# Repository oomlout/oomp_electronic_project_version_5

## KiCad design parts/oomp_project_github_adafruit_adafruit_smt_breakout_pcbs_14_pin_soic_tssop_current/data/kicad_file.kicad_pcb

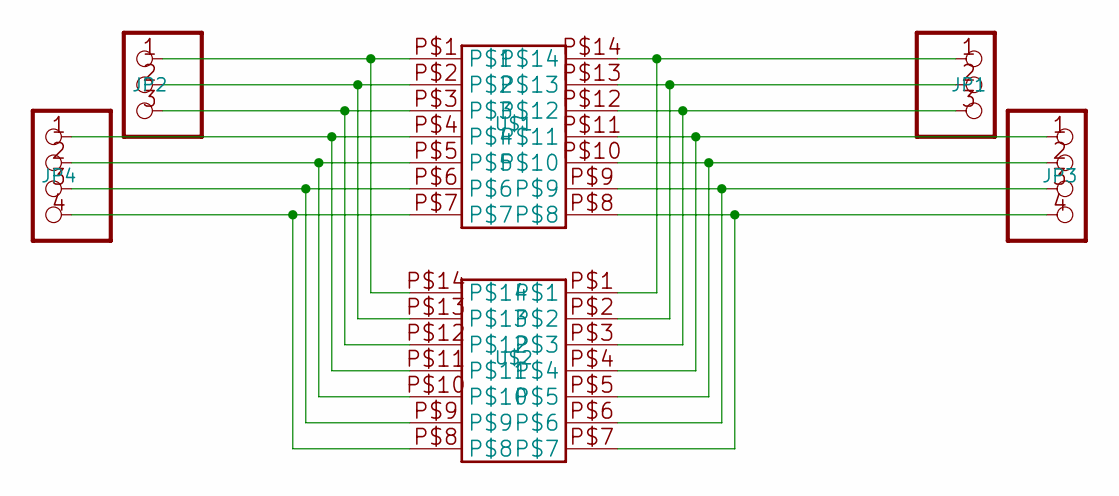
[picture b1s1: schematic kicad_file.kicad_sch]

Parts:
JP1, JP2: PADS-3
JP3, JP4: PADS-4
U$1: 14-PINSOIC-NW; SO14-NW
U$2: 14-PINTSSOP-NW; TSSOP14-NW

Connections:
unnamed: JP2.1, U$1.P$1, U$2.P$14
unnamed: JP2.2, U$1.P$2, U$2.P$13
unnamed: JP2.3, U$1.P$3, U$2.P$12
unnamed: JP4.1, U$1.P$4, U$2.P$11
unnamed: JP4.2, U$1.P$5, U$2.P$10
unnamed: JP4.3, U$1.P$6, U$2.P$9
unnamed: JP4.4, U$1.P$7, U$2.P$8
unnamed: JP1.1, U$1.P$14, U$2.P$1
unnamed: JP1.2, U$1.P$13, U$2.P$2
unnamed: JP1.3, U$1.P$12, U$2.P$3
unnamed: JP3.1, U$1.P$11, U$2.P$4
unnamed: JP3.2, U$1.P$10, U$2.P$5
unnamed: JP3.3, U$1.P$9, U$2.P$6
unnamed: JP3.4, U$1.P$8, U$2.P$7

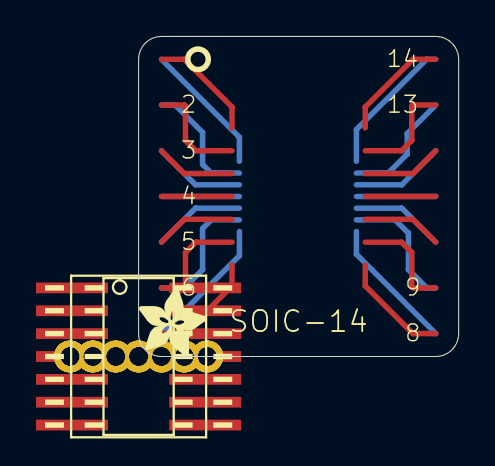
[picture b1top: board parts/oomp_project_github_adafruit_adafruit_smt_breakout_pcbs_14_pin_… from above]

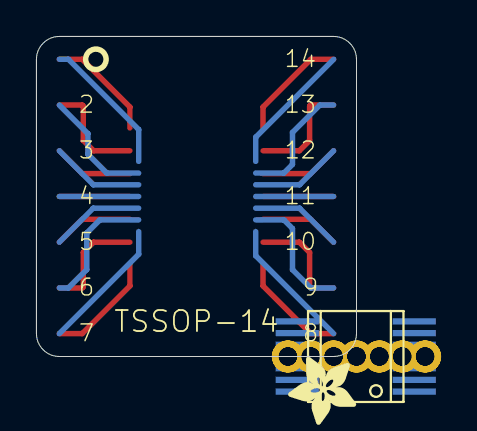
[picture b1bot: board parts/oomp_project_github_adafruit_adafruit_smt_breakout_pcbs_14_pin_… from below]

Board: 2 copper layers, 17.8 x 17.8 mm, 8 parts (2 on the bottom side), 14 nets.

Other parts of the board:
U$3, U$4: ADAFRUIT_3.5MM

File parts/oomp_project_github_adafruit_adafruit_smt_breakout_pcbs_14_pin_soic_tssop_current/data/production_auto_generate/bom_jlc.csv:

Comment,Designator,Footprint,LCSC Part #
,"U$3,U$4",14-pin SOIC+TSSOP-import-fps:ADAFRUIT_3.5MM,
,"JP1,JP2",14-pin SOIC+TSSOP-import-fps:PADS-3,
,"JP3,JP4",14-pin SOIC+TSSOP-import-fps:PADS-4,
14-PINSOIC-NW,U$1,14-pin SOIC+TSSOP-import-fps:SO14-NW,
14-PINTSSOP-NW,U$2,14-pin SOIC+TSSOP-import-fps:TSSOP14-NW,

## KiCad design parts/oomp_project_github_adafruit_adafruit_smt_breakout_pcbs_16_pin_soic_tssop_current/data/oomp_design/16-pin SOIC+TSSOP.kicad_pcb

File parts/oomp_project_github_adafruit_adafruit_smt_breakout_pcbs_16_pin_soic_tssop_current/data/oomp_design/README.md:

# OOMP KiCad design copy

Open `16-pin SOIC+TSSOP.kicad_pro` (or the `.kicad_pcb` / `.kicad_sch`) in KiCad. Local OOMP libraries are under `libraries/`. Original inputs are preserved in [../original/](../original/).

Only verified unchanged installed KiCad defaults were renamed. Modified, custom, unmatched and unavailable items remain unchanged. Soldering variants are never swapped during conversion. Existing pad coordinates, nets and UUIDs are preserved.

See [conversion_report.yaml](conversion_report.yaml) for every conversion and skip. Copy this directory before editing; regeneration refuses to overwrite edited design files.

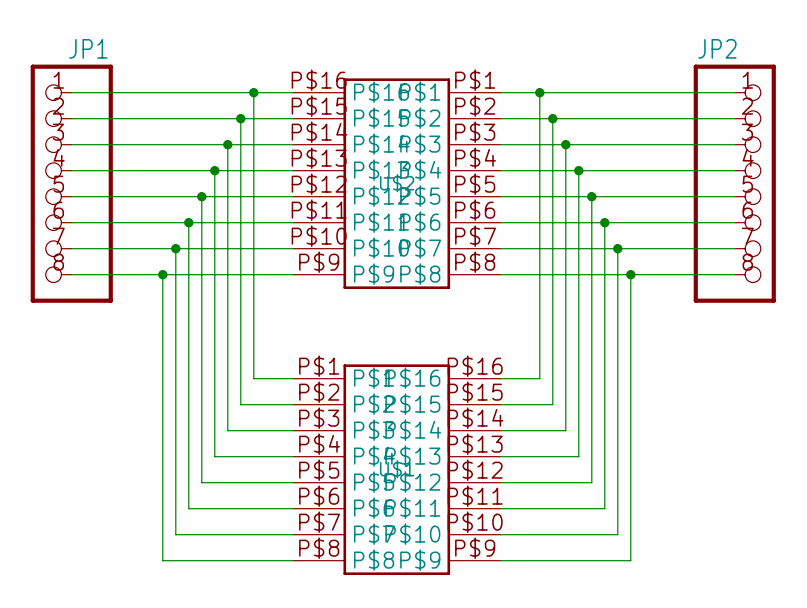
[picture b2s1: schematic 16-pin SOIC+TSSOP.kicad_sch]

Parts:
JP1, JP2: PADS-8CLEANBIG; PADS-8
U$1: 16-PINSOIC-NW; SO16-NW
U$2: 16-PINTSSOP-NW; TSSOP16-NW

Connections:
unnamed: JP1.1, U$1.P$1, U$2.P$16
unnamed: JP1.2, U$1.P$2, U$2.P$15
unnamed: JP1.3, U$1.P$3, U$2.P$14
unnamed: JP1.4, U$1.P$4, U$2.P$13
unnamed: JP1.6, U$1.P$6, U$2.P$11
unnamed: JP1.7, U$1.P$7, U$2.P$10
unnamed: JP1.8, U$1.P$8, U$2.P$9
unnamed: JP2.1, U$1.P$16, U$2.P$1
unnamed: JP2.2, U$1.P$15, U$2.P$2
unnamed: JP2.3, U$1.P$14, U$2.P$3
unnamed: JP2.4, U$1.P$13, U$2.P$4
unnamed: JP2.5, U$1.P$12, U$2.P$5
unnamed: JP2.6, U$1.P$11, U$2.P$6
unnamed: JP2.7, U$1.P$10, U$2.P$7
unnamed: JP2.8, U$1.P$9, U$2.P$8
unnamed: JP1.5, U$1.P$5, U$2.P$12

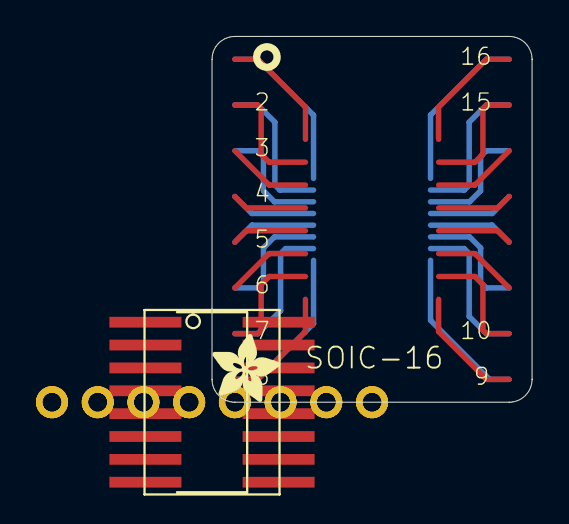
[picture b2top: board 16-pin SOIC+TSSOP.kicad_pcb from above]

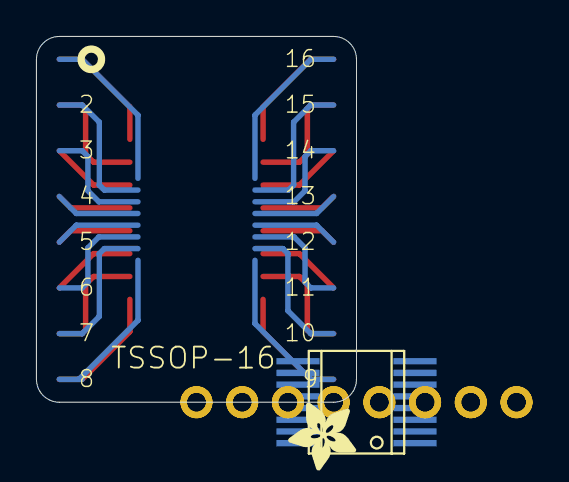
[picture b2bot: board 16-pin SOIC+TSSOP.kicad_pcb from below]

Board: 2 copper layers, 17.8 x 20.3 mm, 6 parts (2 on the bottom side), 16 nets.

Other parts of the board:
U$3, U$4: ADAFRUIT_3.5MM

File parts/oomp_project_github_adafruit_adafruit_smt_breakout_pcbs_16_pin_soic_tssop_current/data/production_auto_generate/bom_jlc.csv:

Comment,Designator,Footprint,LCSC Part #
,"U$3,U$4",16-pin SOIC+TSSOP-import-fps:ADAFRUIT_3.5MM,
,"JP1,JP2",16-pin SOIC+TSSOP-import-fps:PADS-8,
16-PINSOIC-NW,U$1,16-pin SOIC+TSSOP-import-fps:SO16-NW,
16-PINTSSOP-NW,U$2,16-pin SOIC+TSSOP-import-fps:TSSOP16-NW,

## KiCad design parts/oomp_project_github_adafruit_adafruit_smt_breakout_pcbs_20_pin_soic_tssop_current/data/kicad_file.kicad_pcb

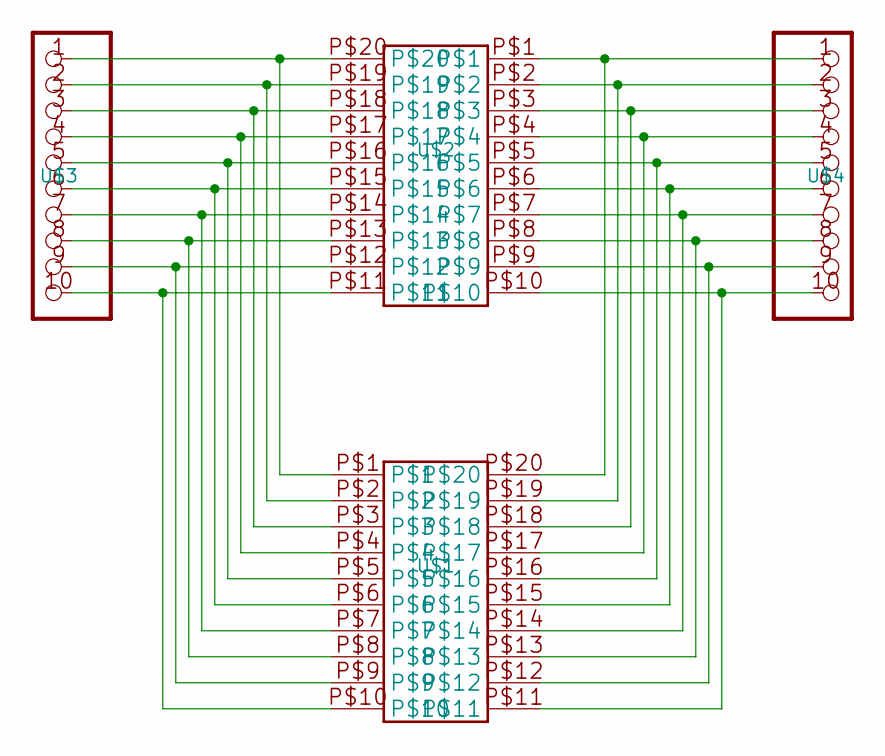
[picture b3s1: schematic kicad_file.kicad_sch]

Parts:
U$1: 20-PINSOIC-NW; SO20-NW
U$2: 20-PINTSSOP-NW; TSSOP20-NW
U$3, U$4: PADS-10

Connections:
unnamed: U$1.P$1, U$2.P$20, U$3.1
unnamed: U$1.P$2, U$2.P$19, U$3.2
unnamed: U$1.P$3, U$2.P$18, U$3.3
unnamed: U$1.P$4, U$2.P$17, U$3.4
unnamed: U$1.P$5, U$2.P$16, U$3.5
unnamed: U$1.P$6, U$2.P$15, U$3.6
unnamed: U$1.P$7, U$2.P$14, U$3.7
unnamed: U$1.P$8, U$2.P$13, U$3.8
unnamed: U$1.P$9, U$2.P$12, U$3.9
unnamed: U$1.P$10, U$2.P$11, U$3.10
unnamed: U$1.P$20, U$2.P$1, U$4.1
unnamed: U$1.P$19, U$2.P$2, U$4.2
unnamed: U$1.P$18, U$2.P$3, U$4.3
unnamed: U$1.P$17, U$2.P$4, U$4.4
unnamed: U$1.P$16, U$2.P$5, U$4.5
unnamed: U$1.P$15, U$2.P$6, U$4.6
unnamed: U$1.P$14, U$2.P$7, U$4.7
unnamed: U$1.P$13, U$2.P$8, U$4.8
unnamed: U$1.P$12, U$2.P$9, U$4.9
unnamed: U$1.P$11, U$2.P$10, U$4.10

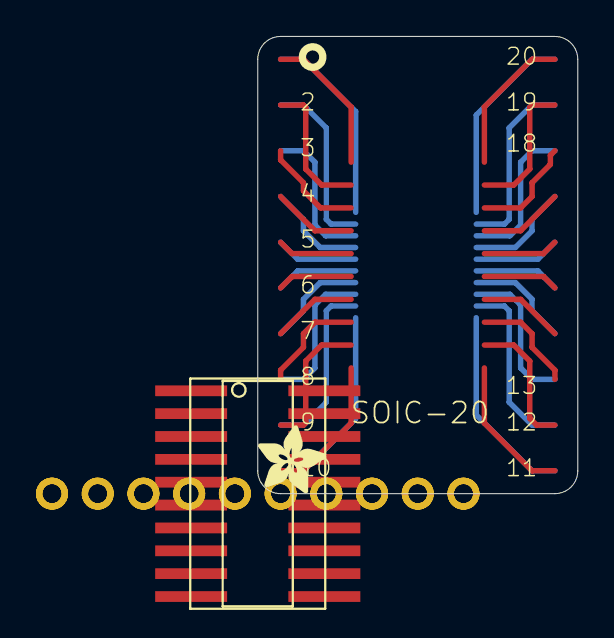
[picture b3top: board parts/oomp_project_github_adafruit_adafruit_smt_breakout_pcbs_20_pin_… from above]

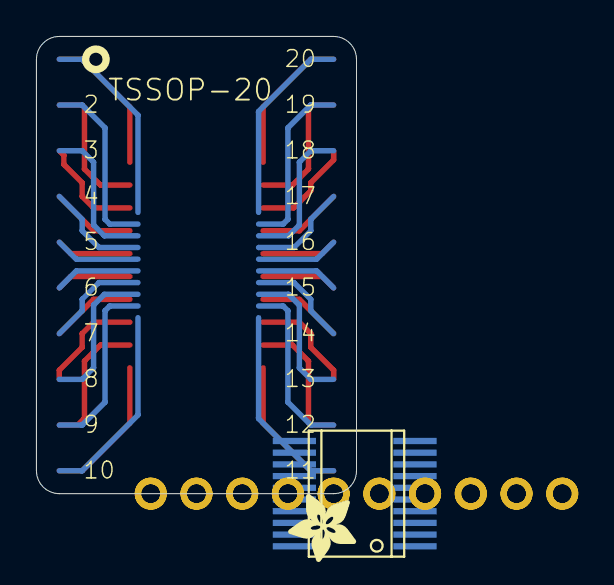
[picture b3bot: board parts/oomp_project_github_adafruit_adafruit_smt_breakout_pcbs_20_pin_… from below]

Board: 2 copper layers, 17.8 x 25.4 mm, 6 parts (2 on the bottom side), 20 nets.

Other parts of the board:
U$5, U$6: ADAFRUIT_3.5MM

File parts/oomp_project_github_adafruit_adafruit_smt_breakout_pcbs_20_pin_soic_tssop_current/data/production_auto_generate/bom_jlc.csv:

Comment,Designator,Footprint,LCSC Part #
,"U$5,U$6",20-pin SOIC+TSSOP-import-fps:ADAFRUIT_3.5MM,
,"U$3,U$4",20-pin SOIC+TSSOP-import-fps:PADS-10,
20-PINSOIC-NW,U$1,20-pin SOIC+TSSOP-import-fps:SO20-NW,
20-PINTSSOP-NW,U$2,20-pin SOIC+TSSOP-import-fps:TSSOP20-NW,

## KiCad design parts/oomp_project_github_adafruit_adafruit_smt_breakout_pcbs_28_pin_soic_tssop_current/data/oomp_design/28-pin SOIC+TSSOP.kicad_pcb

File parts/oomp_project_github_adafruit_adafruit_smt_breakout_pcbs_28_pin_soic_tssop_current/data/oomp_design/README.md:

# OOMP KiCad design copy

Open `28-pin SOIC+TSSOP.kicad_pro` (or the `.kicad_pcb` / `.kicad_sch`) in KiCad. Local OOMP libraries are under `libraries/`. Original inputs are preserved in [../original/](../original/).

Only verified unchanged installed KiCad defaults were renamed. Modified, custom, unmatched and unavailable items remain unchanged. Soldering variants are never swapped during conversion. Existing pad coordinates, nets and UUIDs are preserved.

See [conversion_report.yaml](conversion_report.yaml) for every conversion and skip. Copy this directory before editing; regeneration refuses to overwrite edited design files.

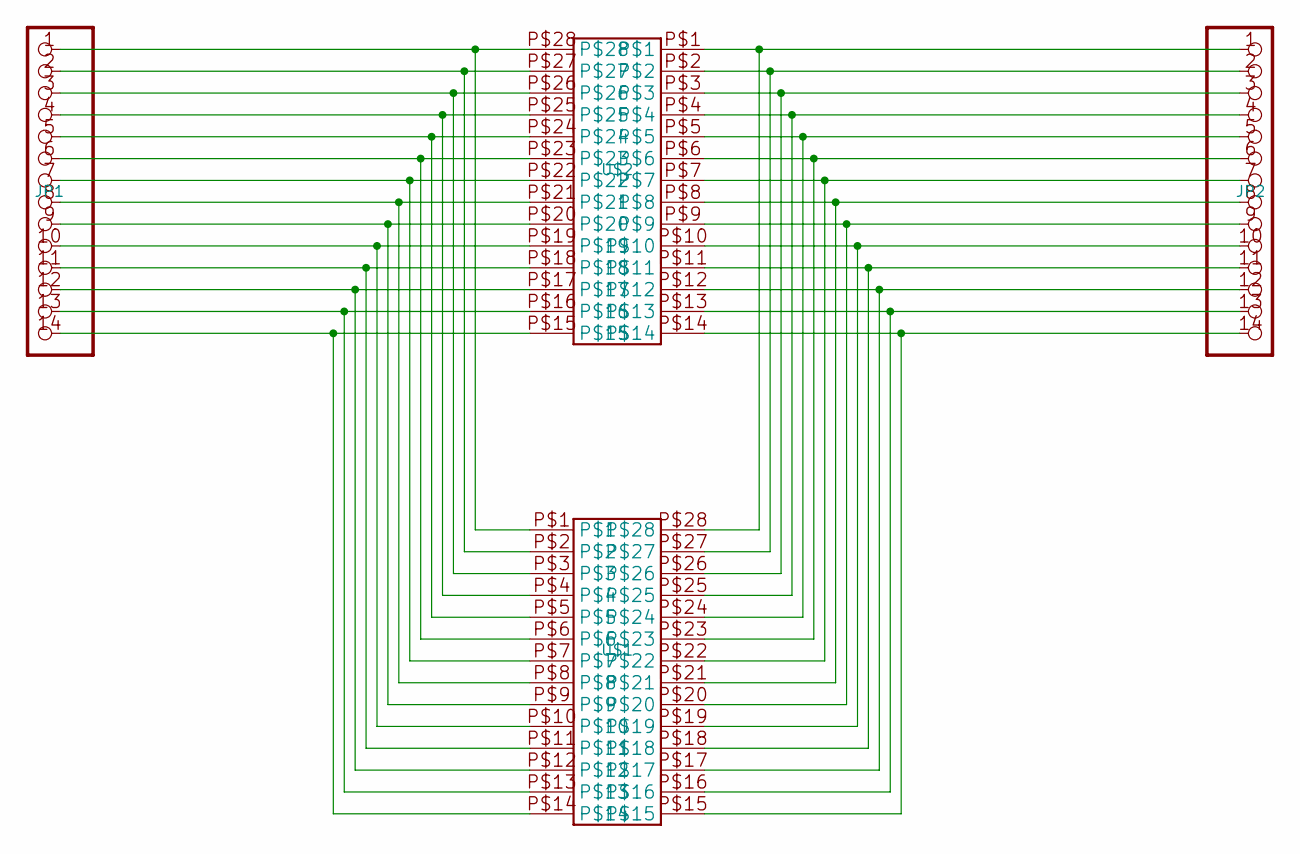
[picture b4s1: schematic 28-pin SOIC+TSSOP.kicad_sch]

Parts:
JP1, JP2: PADS-14
U$1: 28-PINSOIC-NW; SO28-NW
U$2: 28-PINTSSOP-NW; TSSOP28-NW

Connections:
unnamed: JP1.1, U$1.P$1, U$2.P$28
unnamed: JP1.2, U$1.P$2, U$2.P$27
unnamed: JP1.3, U$1.P$3, U$2.P$26
unnamed: JP1.4, U$1.P$4, U$2.P$25
unnamed: JP1.5, U$1.P$5, U$2.P$24
unnamed: JP1.6, U$1.P$6, U$2.P$23
unnamed: JP1.7, U$1.P$7, U$2.P$22
unnamed: JP1.8, U$1.P$8, U$2.P$21
unnamed: JP1.9, U$1.P$9, U$2.P$20
unnamed: JP1.10, U$1.P$10, U$2.P$19
unnamed: JP1.11, U$1.P$11, U$2.P$18
unnamed: JP1.12, U$1.P$12, U$2.P$17
unnamed: JP1.14, U$1.P$14, U$2.P$15
unnamed: JP2.1, U$1.P$28, U$2.P$1
unnamed: JP2.2, U$1.P$27, U$2.P$2
unnamed: JP2.3, U$1.P$26, U$2.P$3
unnamed: JP2.4, U$1.P$25, U$2.P$4
unnamed: JP2.5, U$1.P$24, U$2.P$5
unnamed: JP2.6, U$1.P$23, U$2.P$6
unnamed: JP2.7, U$1.P$22, U$2.P$7
unnamed: JP2.8, U$1.P$21, U$2.P$8
unnamed: JP2.9, U$1.P$20, U$2.P$9
unnamed: JP2.10, U$1.P$19, U$2.P$10
unnamed: JP2.11, U$1.P$18, U$2.P$11
unnamed: JP2.12, U$1.P$17, U$2.P$12
unnamed: JP2.13, U$1.P$16, U$2.P$13
unnamed: JP2.14, U$1.P$15, U$2.P$14
unnamed: JP1.13, U$1.P$13, U$2.P$16

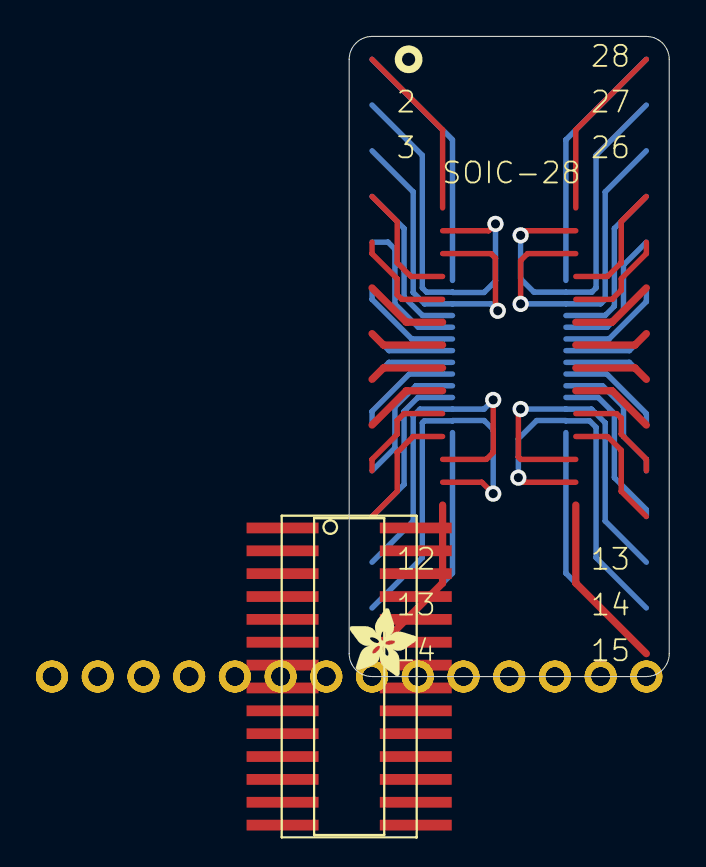
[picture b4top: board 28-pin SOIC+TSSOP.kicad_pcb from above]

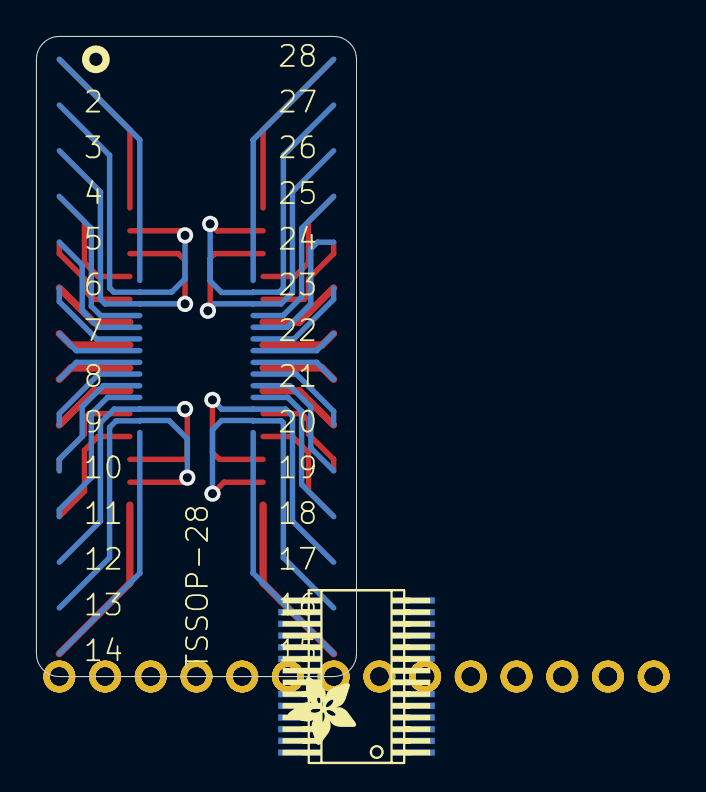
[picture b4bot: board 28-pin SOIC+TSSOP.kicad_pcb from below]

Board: 2 copper layers, 17.8 x 35.6 mm, 6 parts (2 on the bottom side), 28 nets.

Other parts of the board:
U$3, U$4: ADAFRUIT_3.5MM

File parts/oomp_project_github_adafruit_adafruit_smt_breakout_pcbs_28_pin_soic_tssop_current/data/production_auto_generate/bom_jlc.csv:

Comment,Designator,Footprint,LCSC Part #
,"U$3,U$4",28-pin SOIC+TSSOP-import-fps:ADAFRUIT_3.5MM,
,"JP1,JP2",28-pin SOIC+TSSOP-import-fps:PADS-14,
28-PINSOIC-NW,U$1,28-pin SOIC+TSSOP-import-fps:SO28-NW,
28-PINTSSOP-NW,U$2,28-pin SOIC+TSSOP-import-fps:TSSOP28-NW,
